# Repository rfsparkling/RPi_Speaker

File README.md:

Integrated active amplifier PCB for Rapsberry Pi (versions 1,2 and 3). On board LM386 amplifier do the amplification of the weak PWM audio signal coming out of RPi GPIO.
Also an on board low pass filter helps reconsturging the analog audio signal from PWM. 

Amplifier board built, find test video on Youtube here: http://bit.ly/rpi_speaker

------------
Installation
------------

Latest Raspbian OS has Pigpio software pre-installed, this handles GPIO alternative function. 
So just strart it and configure GPIO18 into ALT5 mode in RPi 2 and 3 (routing audio PWM signal to amplifier PCB):
In RPi 1 PWM audio can acces at GPIO12 port, see schematic.

Commands:

```
sudo pigpiod # start daemon
pigs m 18 5 # set GPIO18 to mode ALT5, RPi 2 and RPi 3 
```

Playing music with for example omxplayer (included in Raspbian) take care to route audio signal to PWM port and not HDMI output (-o local switch below).
You can listen internet stream or offline audio files. This example starts a music station:

```
omxplayer -o local http://bbcmedia.ic.llnwd.net/stream/bbcmedia_6music_mf_p
```

-----------------------
Alternative GPIO config
-----------------------

If Pigpio doesn't work for you, try this method:

https://www.raspberrypi.org/forums/viewtopic.php?f=44&t=39138

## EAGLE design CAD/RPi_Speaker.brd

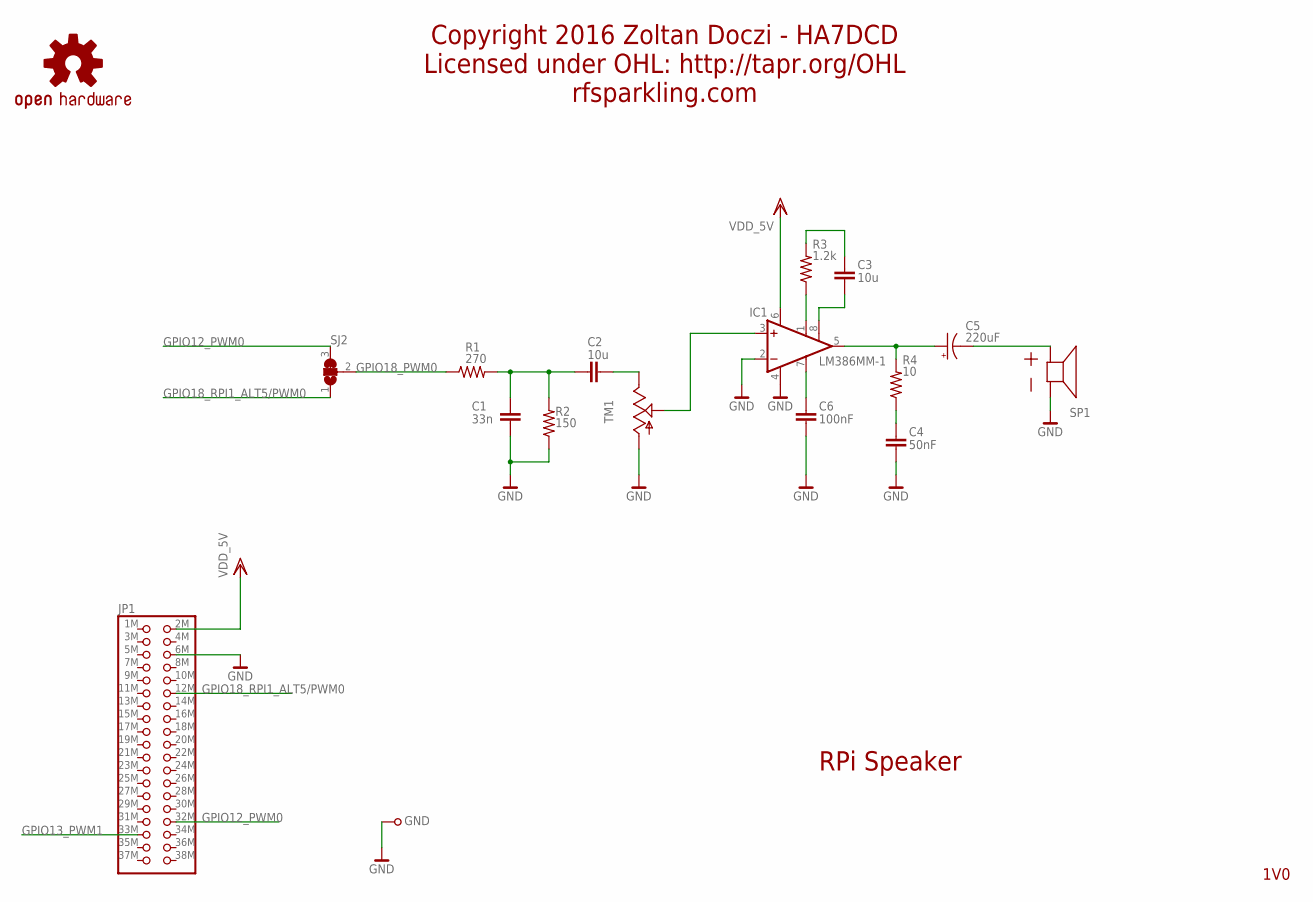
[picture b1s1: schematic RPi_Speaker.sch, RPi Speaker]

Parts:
C1: 33n; 0603
C2, C3: 10u; 0603
C4: 50nF; 0603
C5: 220uF; D/7343-31R
C6: 100nF; 0603
GND: TESTPOINT39MIL; TESTPOINT1,0
IC1: LM386MM-1; MMSOP08
JP1: PINHD-2X18/MIRROR; 2X18_MIRROR
R1: 270; R0402
R2: 150; R0402
R3: 1.2k; R0402
R4: 10; R0402
SJ2: JUMPER_SMD_3A; JUMPER_SMD_SJ2A
SP1: SPEAKER_ABS-210-RC; SPEAKER_ABS-210-RC_50MM
TM1: TRIM; 6MM
U$15: OSHW-LOGOS; OSHW-LOGO-S

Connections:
GND: C1.1, C4.2, C6.2, GND.1, IC1.2 (-IN), IC1.4 (GND), JP1.6M (6), R2.1, SP1.N (-), TM1.A
GPIO12_PWM0: JP1.32M (32), SJ2.3
GPIO13_PWM1: JP1.33M (33)
GPIO18_PWM0: R1.1, SJ2.2
GPIO18_RPI1_ALT5/PWM0: JP1.12M (12), SJ2.1
unnamed: C1.2, C2.2, R1.2, R2.2
unnamed: C2.1, TM1.E
unnamed: IC1.3 (+IN), TM1.S
unnamed: IC1.1 (GAIN), R3.1
unnamed: C3.1, R3.2
unnamed: C3.2, IC1.8 (GAIN)
unnamed: C5.+, IC1.5 (OUT), R4.2
unnamed: C4.1, R4.1
unnamed: C5.-, SP1.P (+)
unnamed: C6.1, IC1.7 (BYPASS)
VDD_5V: IC1.6 (VS), JP1.2M (2)

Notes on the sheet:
RPi Speaker
1V0
Copyright 2016 Zoltan Doczi - HA7DCD Licensed under OHL: http://tapr.org/OHL rfsparkling.com

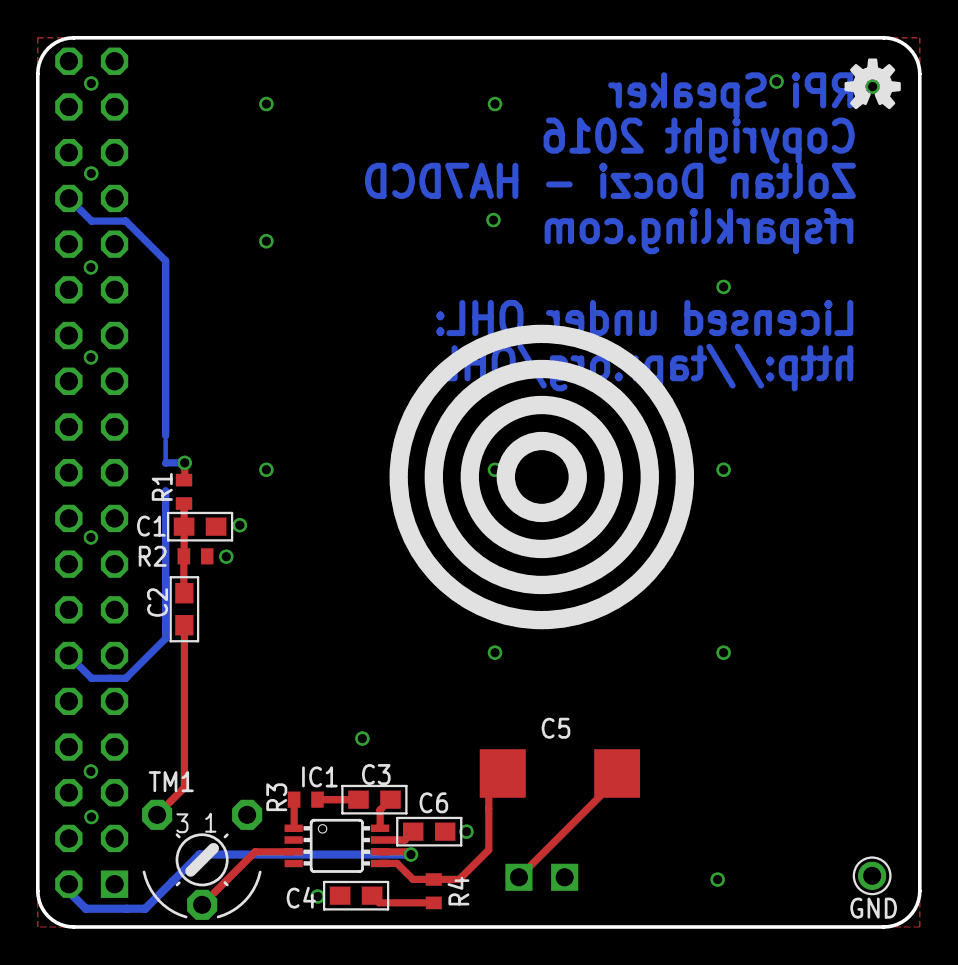
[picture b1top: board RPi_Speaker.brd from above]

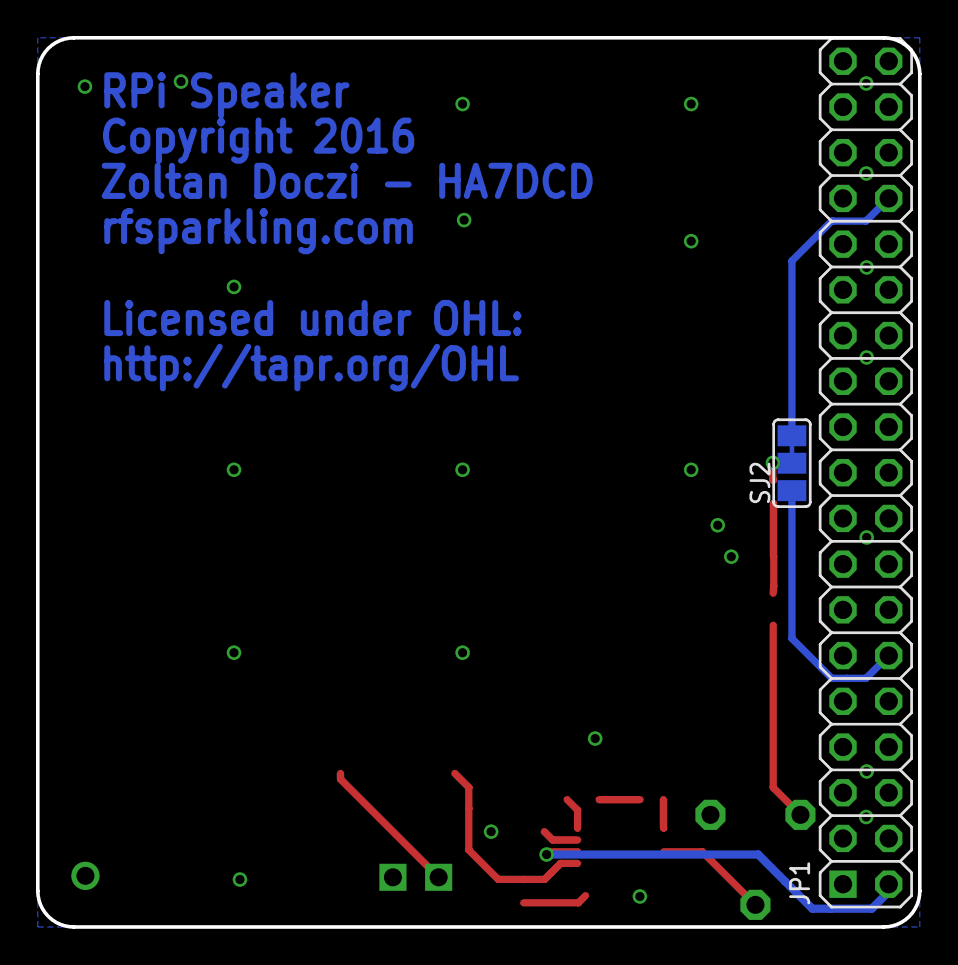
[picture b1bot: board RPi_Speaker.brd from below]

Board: 2 copper layers, 49.0 x 49.4 mm, 17 parts (2 on the bottom side), 15 nets.

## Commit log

2016-10-02 adding RPi Speaker CAD, CAM, PDF files
    Fully integrated, compact active speaker shield for all Raspberry Pi
    versions
2016-10-02 adding real photo
2016-10-02 adding gpio configuration and music player example
2016-10-02 code snippets
